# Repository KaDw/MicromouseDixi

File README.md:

# Micromouse Dixi #
	
|  |  |
| ----- | ----- |
| Width   | 79mm  |
| Length  | 95mm  |
| Weight  |   |
| Wheels  | 3D printed wheels + MZT301-20 tyres  |
| Microcontroller  | STM32F405RGT6  |
| Gear ratio  | 27:42  |
| Motor  | Pololu 5:1 HPCB  |
| Encoders  | AS55147P  |
| Battery  | Li-Pol Dualsky 7.4V 150mAh 20C  |
| Motor Driver  | TB6612FNG  |
| Sensor | TEFT4300 + SFH4545 X 6  |
| Gyro | MPU6050  |

[BOM](https://docs.google.com/spreadsheets/d/1-OBliDhJaHepW5BqGZAOIfc_tJH4ITr39Bejxq-Zry4/edit?usp=sharing)

### Development tools ###

* STM32CubeMX Version 4.17.0
* HAL Libraries - FW_F4 V1.13.1
* Keil uVision 5.21a
* EagleCAD 7.7
* Autodesk Inventor 2016

Development tools available [here](https://drive.google.com/open?id=0B6SlddUSFtelRTBFR0EwWk1qT1k)

### Setup ###

* CubeMX setup
You can get HAL libraries by going to Help->Install New Libraries->Firmware Package for Family STM32F4.
...

### Who do I talk to? ###

* Karol Trzciński k.trzcinski95@gmail.com
* Karol Dworakowski karol1dw@gmail.com

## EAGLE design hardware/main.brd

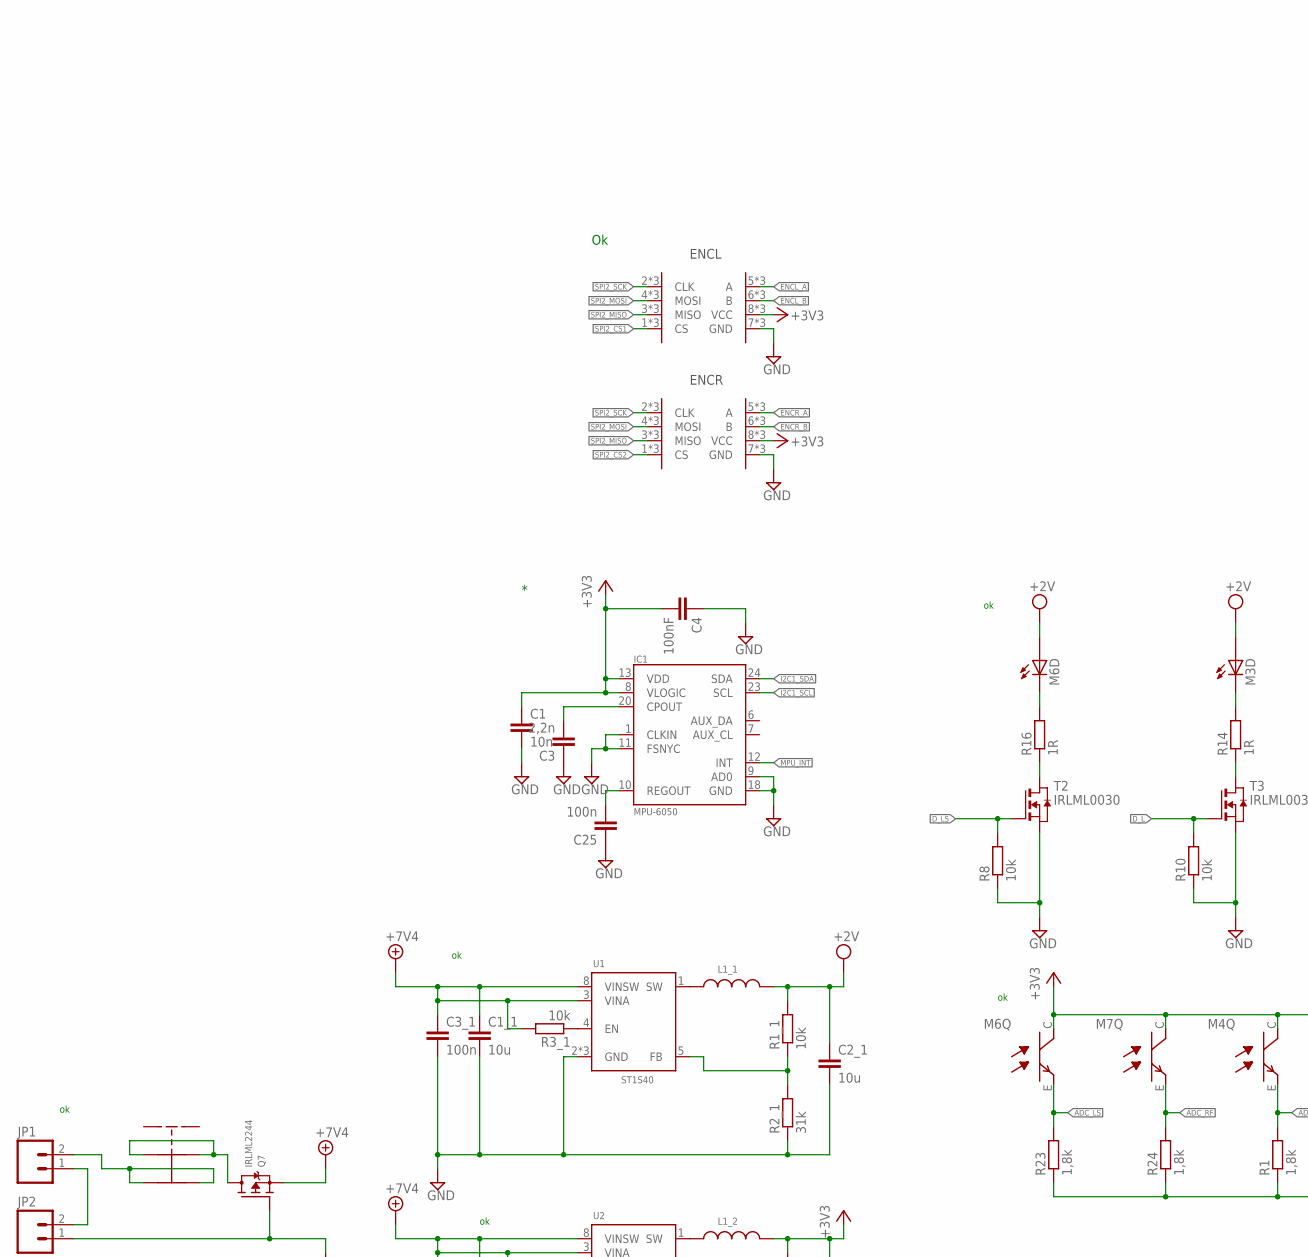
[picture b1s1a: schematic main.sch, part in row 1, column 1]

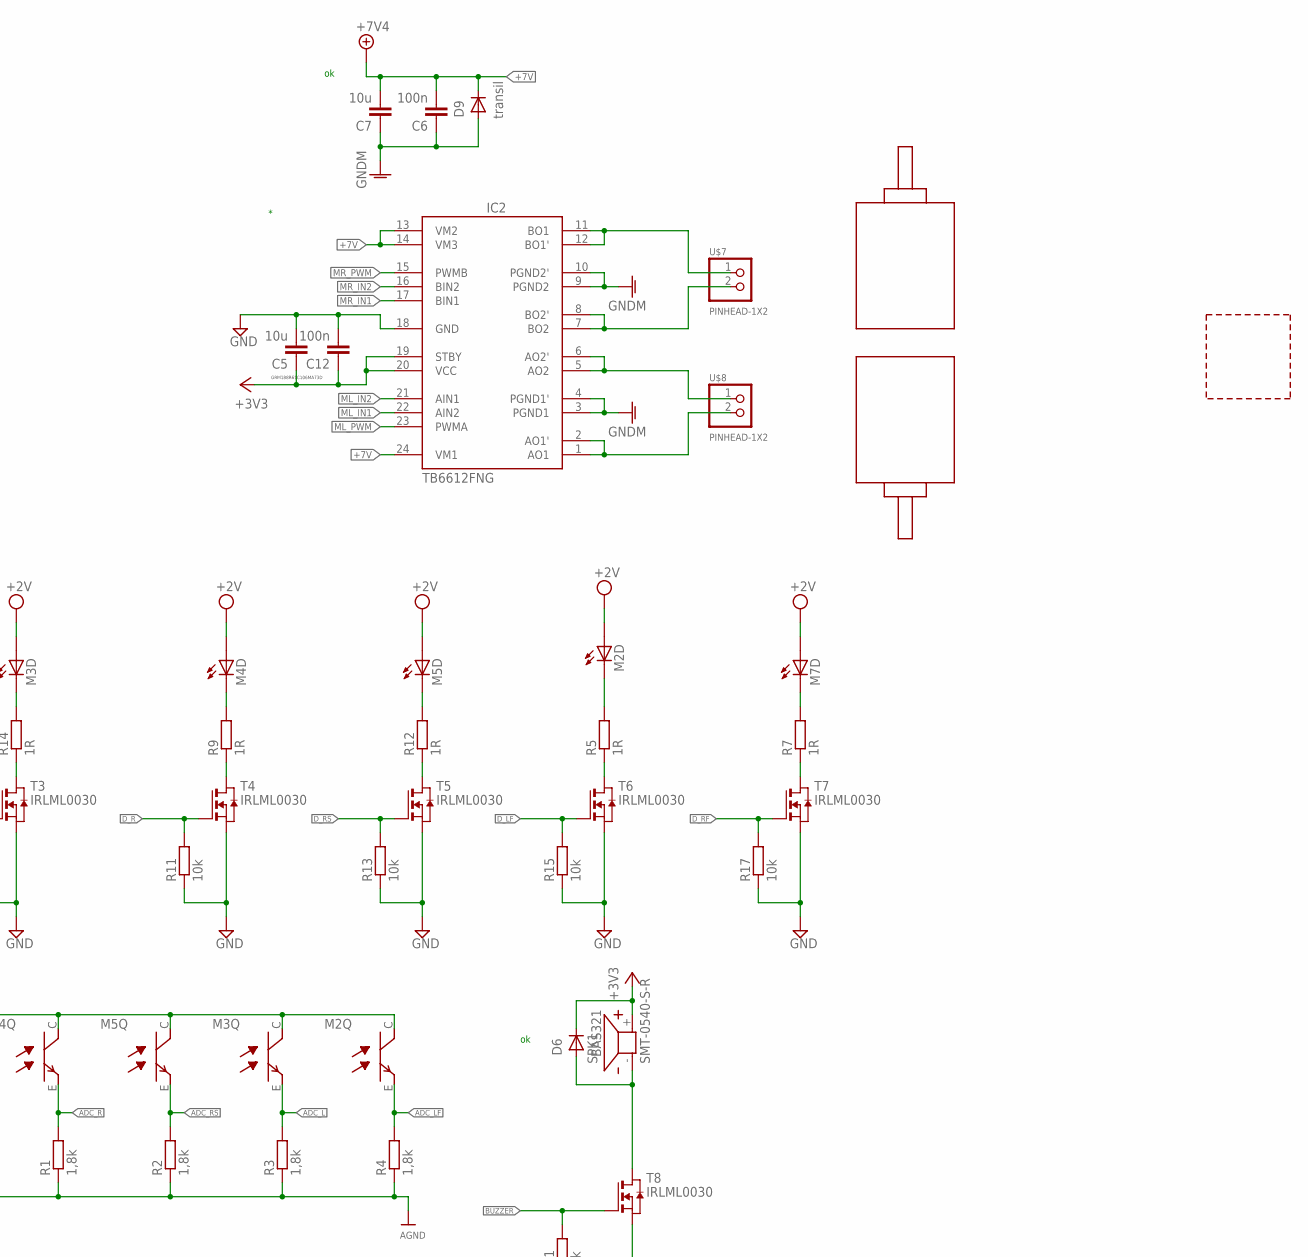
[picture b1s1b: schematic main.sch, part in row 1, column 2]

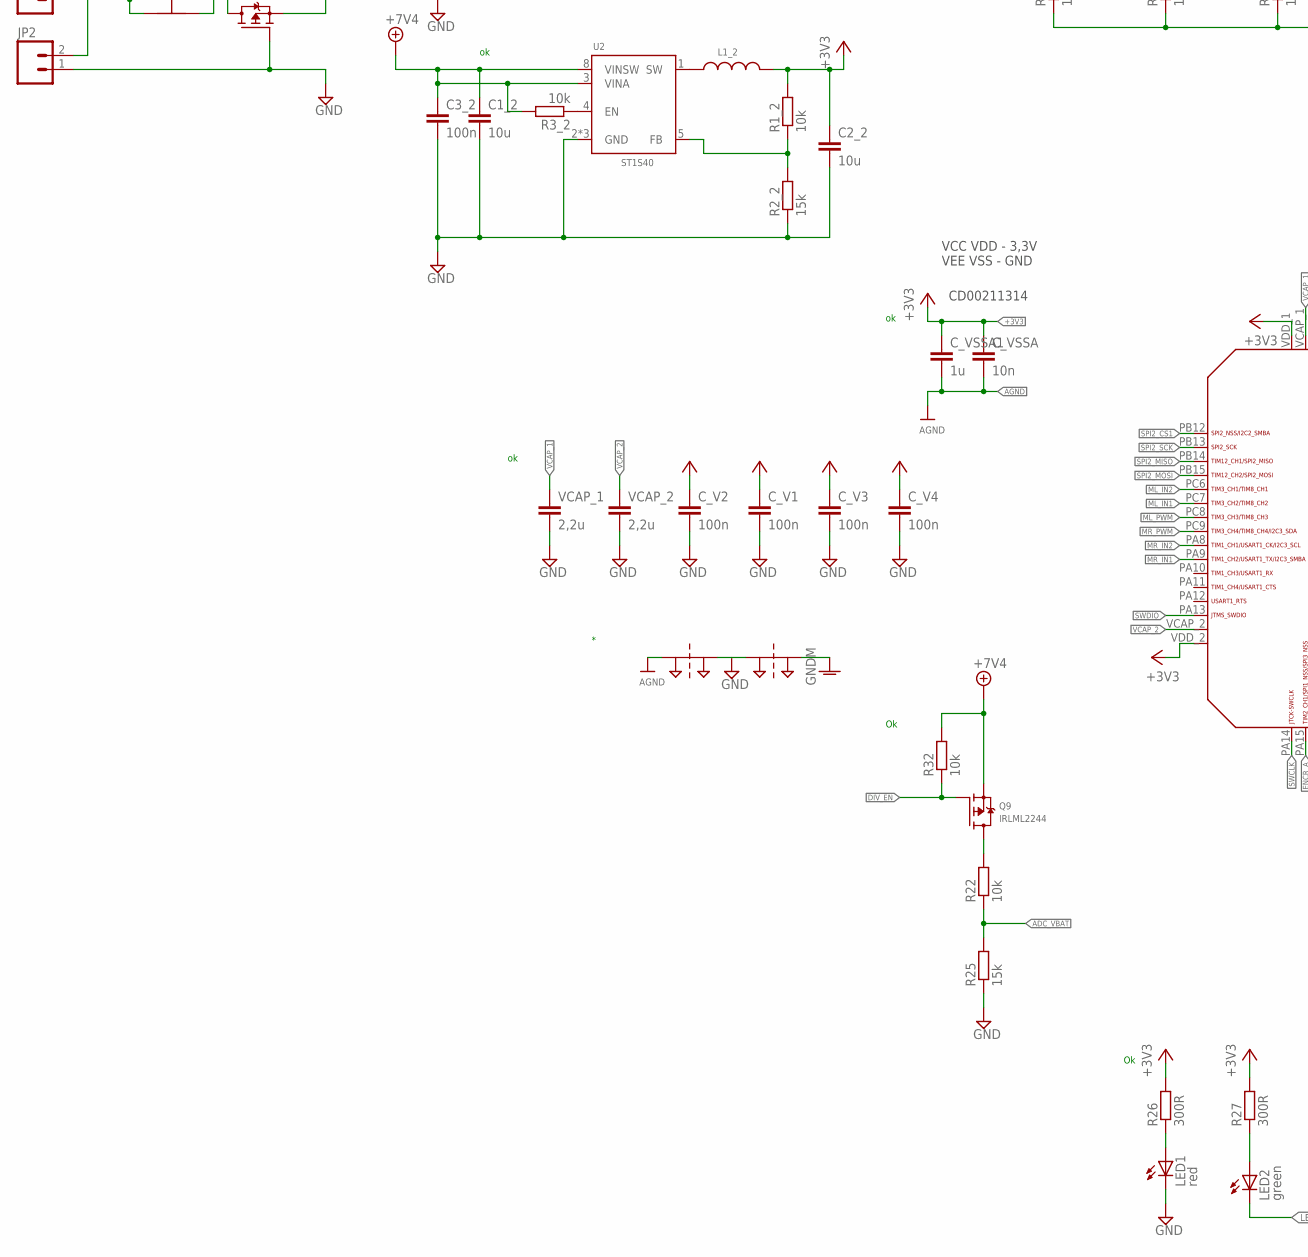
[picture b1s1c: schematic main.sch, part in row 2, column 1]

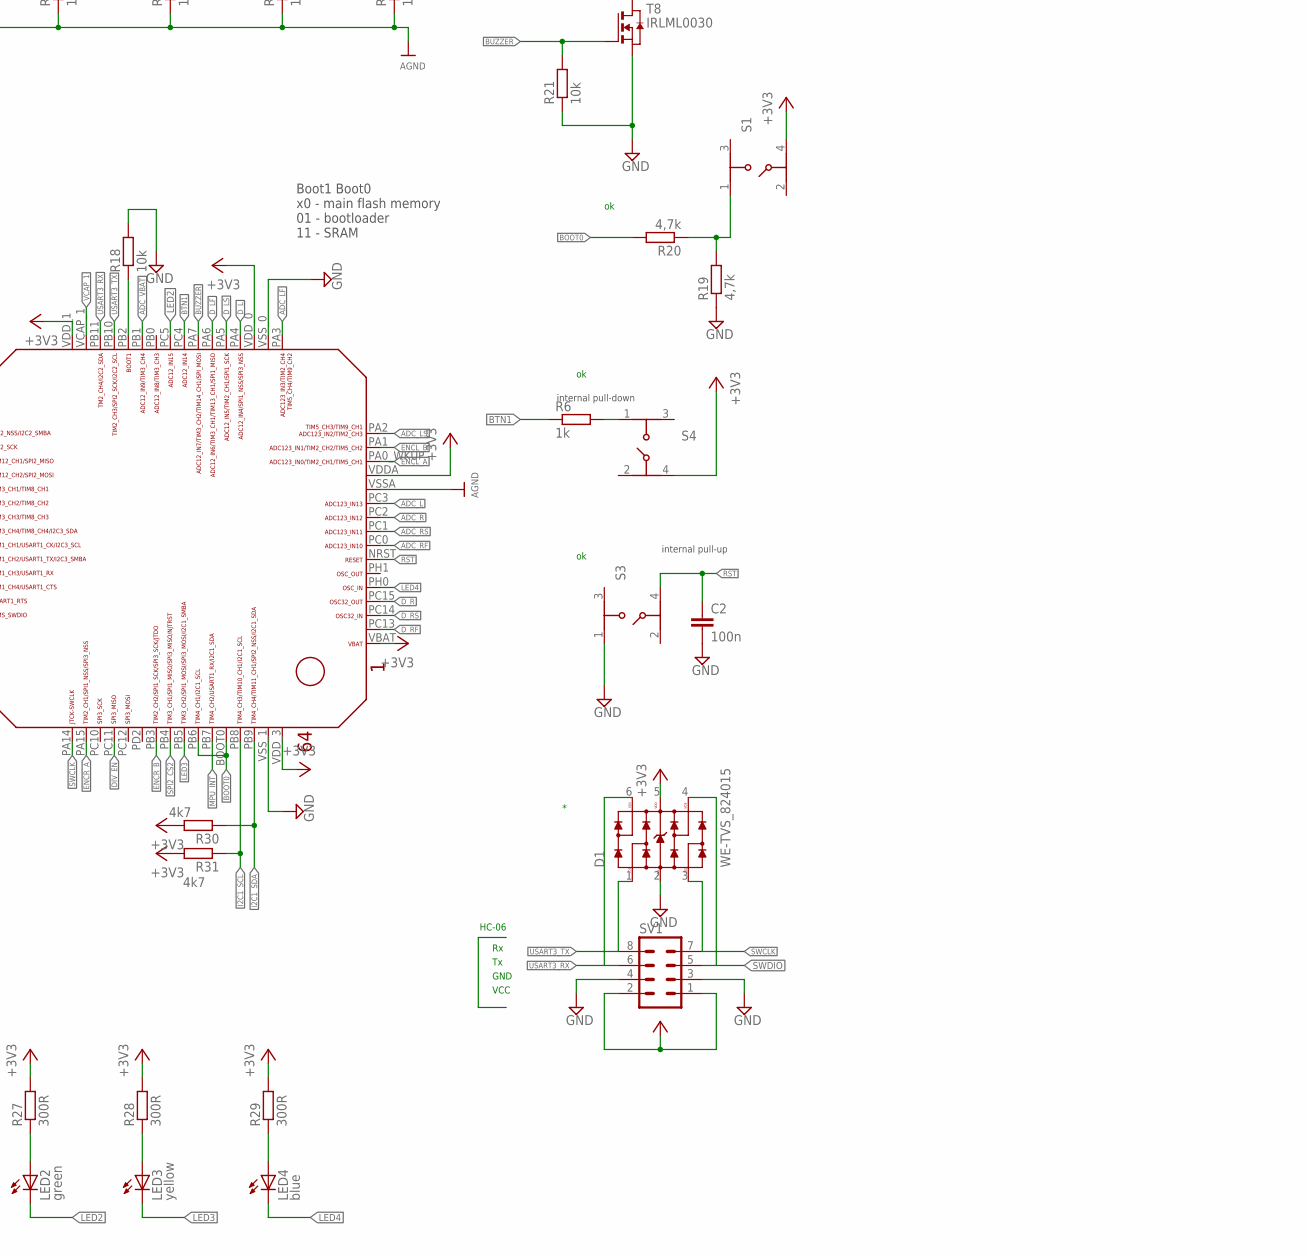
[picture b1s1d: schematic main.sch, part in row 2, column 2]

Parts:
C1: 10n; C0603
C1_1, C1_2, C5: 10u; C0805
C2, C3_1, C3_2, C6, C12, C25: 100n; C0603
C2_1, C2_2, C7: 10u; C1206
C3: 2,2n; C0603
C4: 100nF; C0603
C_V1, C_V2, C_V3, C_V4: 100n; C0603
C_VSSA: 10n; C0603
C_VSSA1: 1u; C0603
D1: WE-TVS_824015; WE-TVS_SOT23-6L
D6: BAS321; SOD323(F)
D9: transil; SOD323(F)
IC1: MPU-6050; QFN.24.4X4
IC2: TB6612FNG; SSOP24
JP1, JP2: M02POLAR; MOLEX-1X2
L1: LABITYNT; LABIRYNT
L1_1: WE-MAIA_3015_78438335068; WE-MAIA_3015
L1_2: WE-MAIA_3015_78438335033; WE-MAIA_3015
LED1: red; SML1206
LED2: green; SML1206
LED3: yellow; SML1206
LED4: blue; SML1206
M1: MOTOR_MOUNT_V2
M2, M3, M4, M5, M6, M7: LED_MOUNT
OFF: PRZELACZNIK_SUWAKOWY
PT1, PT2: 2PT_GND_TIE
Q7, Q9: IRLML2244; SOT23-R
R1, R2, R3, R4, R23, R24: 1,8k; R0603
R1_1, R1_2, R3_1, R3_2, R8, R10, R11, R13, R15, R17, R18, R21, R22, R32: 10k; R0603
R2_1: 31k; R0603
R2_2, R25: 15k; R0603
R5, R7, R9, R12, R14, R16: 1R; R0603
R6: 1k; R0603
R19, R20: 4,7k; R0603
R26, R27, R28, R29: 300R; R0603
R30, R31: 4k7; R0603
S1, S3, S4: 434153017835
SPK1: SMT-0540-S-R
SV1: MA04-2
T2, T3, T4, T5, T6, T7, T8: IRLML0030; SOT-23
U1, U2: ST1S40; SO8
U3: STM32F4X5; STM32F4-LQFP64
U$7, U$8: PINHEAD-1X2; PIHEAD-1X2
U$9, U$10: ENCODER_MOUNT
VCAP_1, VCAP_2: 2,2u; C0603

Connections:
+1.8V: C2_1.1, L1_1.2, M2.+ (A), M3.+ (A), M4.+ (A), M5.+ (A), M6.+ (A), M7.+ (A), R1_1.2
+3V3: C1.1, C2_2.1, C4.2, C5.1, C12.1, C_V1.1, C_V2.1, C_V3.1, C_V4.1, C_VSSA.1, C_VSSA1.1, D1.5 (VDD), D6.1 (K), IC1.8 (VLOGIC), IC1.13 (VDD), IC2.19 (STBY), IC2.20 (VCC), L1_2.2, M2.C, M3.C, M4.C, M5.C, M6.C, M7.C, R1_2.2, R26.2, R27.2, R28.2, R29.2, R30.2, R31.2, S1.4, S4.4, SPK1.+, SV1.1, SV1.2, U3.VBAT, U3.VDDA, U3.VDD_0, U3.VDD_1, U3.VDD_2, U3.VDD_3, U$9.8 (VCC), U$9.8_1 (VCC), U$9.8_2 (VCC), U$10.8 (VCC), U$10.8_1 (VCC), U$10.8_2 (VCC)
+7V: C1_1.1, C1_2.1, C3_1.1, C3_2.1, C6.2, C7.2, D9.1 (K), IC2.13 (VM2), IC2.14 (VM3), IC2.24 (VM1), Q7.2 (S), Q9.2 (S), R3_1.2, R3_2.2, R32.2, U1.3 (VINA), U1.8 (VINSW), U2.3 (VINA), U2.8 (VINSW)
ADC_L: M3.E, R3.2, U3.PC3
ADC_LF: M2.E, R4.2, U3.PA3
ADC_LS: M6.E, R23.2, U3.PA2
ADC_R: M4.E, R1.2, U3.PC2
ADC_RF: M7.E, R24.2, U3.PC0
ADC_RS: M5.E, R2.2, U3.PC1
ADC_VBAT: R22.1, R25.2, U3.PB1
AGND: C_VSSA.2, C_VSSA1.2, PT1.P$1, R1.1, R2.1, R3.1, R4.1, R23.1, R24.1, U3.VSSA
ASDF: R19.2, R20.1, S1.1
BOOT0: R20.2, U3.BOOT0, U3.PB6
BTN1: R6.1, U3.PC4
BUZZER: R21.2, T8.3 (G), U3.PA7
DIV_EN: Q9.1 (G), R32.1, U3.PC11
D_L: R10.2, T3.3 (G), U3.PA4
D_LF: R15.2, T6.3 (G), U3.PA6
D_LS: R8.2, T2.3 (G), U3.PA5
D_R: R11.2, T4.3 (G), U3.PC15
D_RF: R17.2, T7.3 (G), U3.PC13
D_RS: R13.2, T5.3 (G), U3.PC14
ENCL_A: U3.PA0_WKUP (PA0_AKUP), U$9.5 (A), U$9.5_1 (A), U$9.5_2 (A)
ENCL_B: U3.PA1, U$9.6 (B), U$9.6_1 (B), U$9.6_2 (B)
ENCR_A: U3.PA15, U$10.5 (A), U$10.5_1 (A), U$10.5_2 (A)
ENCR_B: U3.PB3, U$10.6 (B), U$10.6_1 (B), U$10.6_2 (B)
GND: C1.2, C1_1.2, C1_2.2, C2.2, C2_1.2, C2_2.2, C3.1, C3_1.2, C3_2.2, C4.1, C5.2, C12.2, C25.1, C_V1.2, C_V2.2, C_V3.2, C_V4.2, D1.2 (GND), IC1.1 (CLKIN), IC1.9 (AD0), IC1.11 (FSNYC), IC1.18 (GND), IC2.18 (GND), JP2.1, LED1.C, PT1.P$2, PT2.P$1, Q7.1 (G), R2_1.1, R2_2.1, R8.1, R10.1, R11.1, R13.1, R15.1, R17.1, R18.2, R19.1, R21.1, R25.1, S3.1, SV1.3, SV1.4, T2.2 (S), T3.2 (S), T4.2 (S), T5.2 (S), T6.2 (S), T7.2 (S), T8.2 (S), U1.2 (GND), U1.6 (GND), U1.7 (GND), U2.2 (GND), U2.6 (GND), U2.7 (GND), U3.VSS_0, U3.VSS_1, U$9.7 (GND), U$9.7_1 (GND), U$9.7_2 (GND), U$10.7 (GND), U$10.7_1 (GND), U$10.7_2 (GND), VCAP_1.2, VCAP_2.2
GNDA: C6.1, C7.1, D9.2 (A), IC2.3 (PGND1), IC2.4 (PGND1'), IC2.9 (PGND2), IC2.10 (PGND2'), PT2.P$2
I2C1_SCL: IC1.23 (SCL), R31.1, U3.PB8
I2C1_SDA: IC1.24 (SDA), R30.1, U3.PB9
LED2: LED2.C, U3.PC5
LED3: LED3.C, U3.PB5
LED4: LED4.C, U3.PH0
ML_IN1: IC2.22 (AIN2), U3.PC7
ML_IN2: IC2.21 (AIN1), U3.PC6
ML_PWM: IC2.23 (PWMA), U3.PC8
MPU_INT: IC1.12 (INT), U3.PB7
MR_IN1: IC2.17 (BIN1), U3.PA9
MR_IN2: IC2.16 (BIN2), U3.PA8
MR_PWM: IC2.15 (PWMB), U3.PC9
unnamed: M7.- (C), R7.2
unnamed: M2.- (C), R5.2
unnamed: R18.1, U3.PB2
unnamed: R5.1, T6.1 (D)
unnamed: R7.1, T7.1 (D)
unnamed: M4.- (C), R9.2
unnamed: R9.1, T4.1 (D)
unnamed: M5.- (C), R12.2
unnamed: R12.1, T5.1 (D)
unnamed: M3.- (C), R14.2
unnamed: R14.1, T3.1 (D)
unnamed: M6.- (C), R16.2
unnamed: R16.1, T2.1 (D)
unnamed: Q9.3 (D), R22.2
unnamed: L1_1.1, U1.1 (SW)
unnamed: L1_2.1, U2.1 (SW)
unnamed: R3_1.1, U1.4 (EN)
unnamed: R3_2.1, U2.4 (EN)
unnamed: JP1.1, JP2.2
unnamed: LED1.A, R26.1
unnamed: LED2.A, R27.1
unnamed: LED3.A, R28.1
unnamed: LED4.A, R29.1
unnamed: R6.2, S4.1
unnamed: C25.2, IC1.10 (REGOUT)
unnamed: D6.2 (A), SPK1.-, T8.1 (D)
unnamed: C3.2, IC1.20 (CPOUT)
unnamed: IC2.1 (AO1), IC2.2 (AO1'), U$8.2
unnamed: IC2.11 (BO1), IC2.12 (BO1'), U$7.1
unnamed: IC2.7 (BO2), IC2.8 (BO2'), U$7.2
unnamed: IC2.5 (AO2), IC2.6 (AO2'), U$8.1
unnamed: OFF.2, OFF.5, Q7.3 (D)
unnamed: JP1.2, OFF.3, OFF.6
unnamed: R1_2.1, R2_2.2, U2.5 (FB)
unnamed: R1_1.1, R2_1.2, U1.5 (FB)
RST: C2.1, S3.4, U3.NRST
SPI2_CS1: U3.PB12, U$9.1 (CS), U$9.1_1 (CS), U$9.1_2 (CS)
SPI2_CS2: U3.PB4, U$10.1 (CS), U$10.1_1 (CS), U$10.1_2 (CS)
SPI2_MISO: U3.PB14, U$9.3 (MISO), U$9.3_1 (MISO), U$9.3_2 (MISO), U$10.3 (MISO), U$10.3_1 (MISO), U$10.3_2 (MISO)
SPI2_MOSI: U3.PB15, U$9.4 (MOSI), U$9.4_1 (MOSI), U$9.4_2 (MOSI), U$10.4 (MOSI), U$10.4_1 (MOSI), U$10.4_2 (MOSI)
SPI2_SCK: U3.PB13, U$9.2 (CLK), U$9.2_1 (CLK), U$9.2_2 (CLK), U$10.2 (CLK), U$10.2_1 (CLK), U$10.2_2 (CLK)
SWCLK: D1.3, SV1.7, U3.PA14
SWDIO: D1.4, SV1.5, U3.PA13
USART3_RX: D1.6, SV1.6, U3.PB11
USART3_TX: D1.1, SV1.8, U3.PB10
VCAP_1: U3.VCAP_1, VCAP_1.1
VCAP_2: U3.VCAP_2, VCAP_2.1

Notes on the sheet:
Boot1 Boot0 x0 - main flash memory 01 - bootloader 11 - SRAM
VCC VDD - 3,3V VEE VSS - GND
internal pull-up
internal pull-down
GND
VCC
HC-06
ENCR
ENCL
CD00211314
GRM188R61C106MA73D

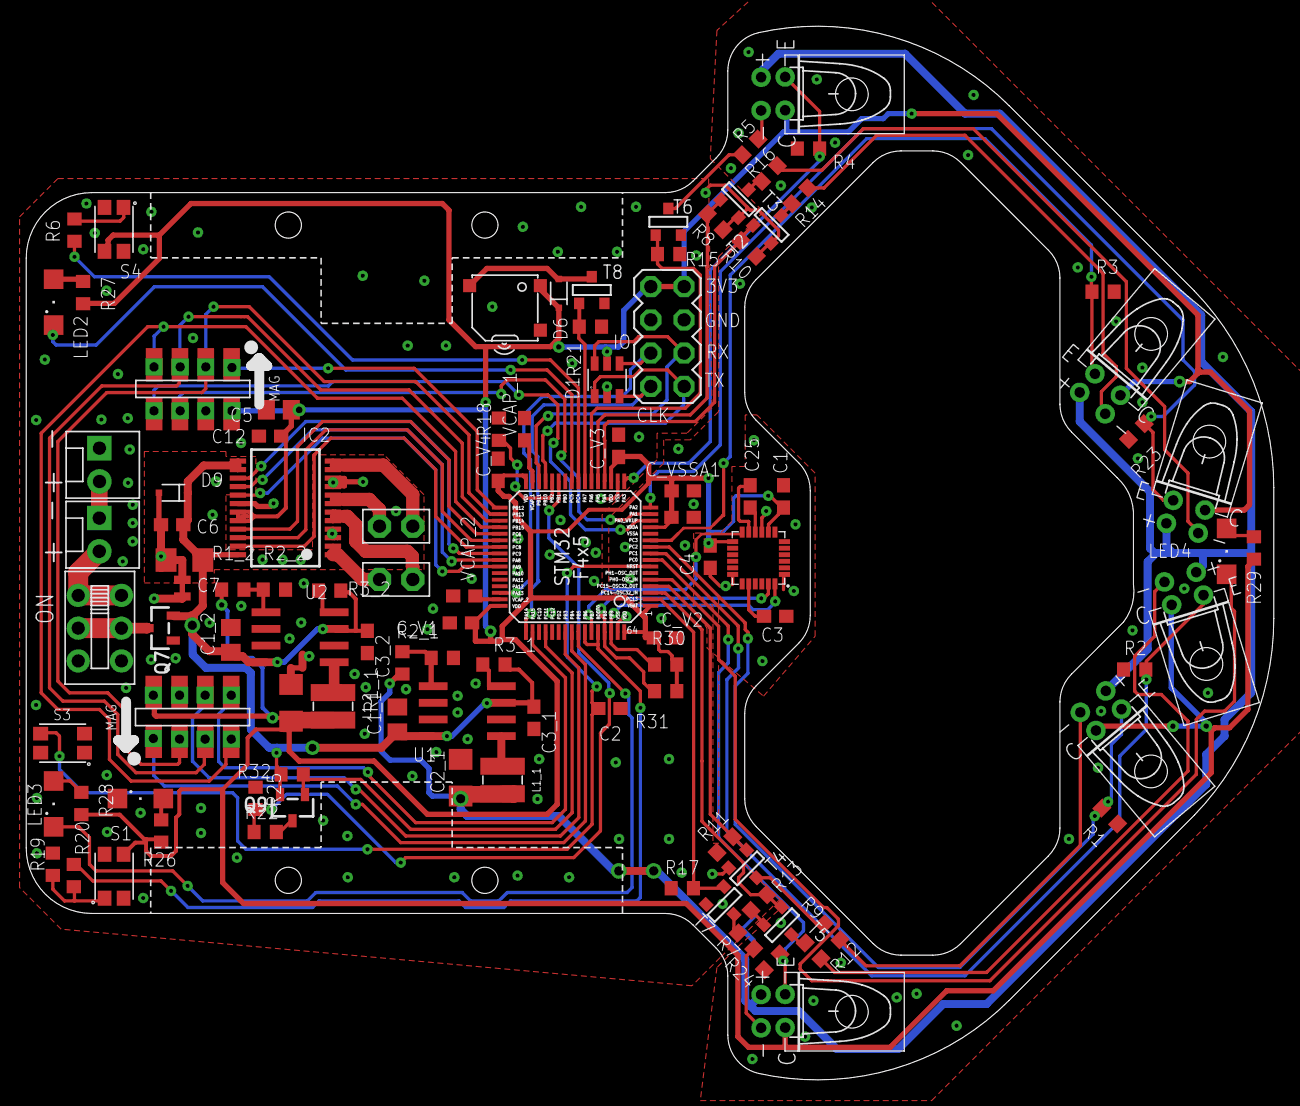
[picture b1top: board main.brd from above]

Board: 2 copper layers, 95.1 x 80.3 mm, 106 parts (1 on the bottom side), 87 nets.

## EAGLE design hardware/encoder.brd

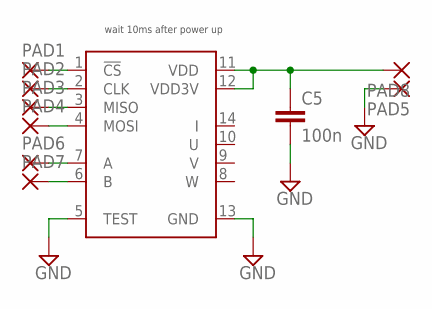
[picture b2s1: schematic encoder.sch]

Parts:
C5: 100n; C0603
PAD1, PAD2, PAD3, PAD4, PAD5, PAD6, PAD7, PAD8: SMD2; SMD1,27-2,54
U$1: AS5147P; TSSOP-14

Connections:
A: PAD6.1, U$1.7 (A)
B: PAD7.1, U$1.6 (B)
CLK: PAD2.1, U$1.2 (CLK)
CS: PAD1.1, U$1.1 (!CS)
GND: C5.2, PAD5.1, U$1.5 (TEST), U$1.13 (GND)
MISO: PAD3.1, U$1.3 (MISO)
MOSI: PAD4.1, U$1.4 (MOSI)
VCC: C5.1, PAD8.1, U$1.11 (VDD), U$1.12 (VDD3V)

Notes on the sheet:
wait 10ms after power up

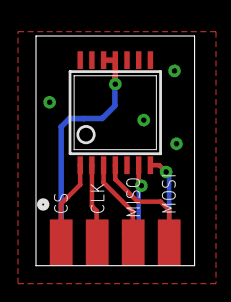
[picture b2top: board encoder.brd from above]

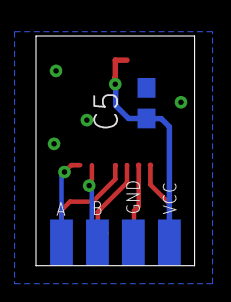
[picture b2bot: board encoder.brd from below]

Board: 2 copper layers, 8.8 x 12.8 mm, 10 parts (5 on the bottom side), 8 nets.

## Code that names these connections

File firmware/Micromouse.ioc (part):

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Mcu.Name=STM32F405RGTx
Mcu.Package=LQFP64
Mcu.UserName=STM32F405RGTx
PA0-WKUP.GPIOParameters=GPIO_Label
PA0-WKUP.GPIO_Label=ENCL_A
PA0-WKUP.Signal=S_TIM5_CH1
PA1.GPIOParameters=GPIO_Label
PA1.GPIO_Label=ENCL_B
PA1.Signal=S_TIM5_CH2
PA13.Mode=Serial_Wire
PA13.Signal=SYS_JTMS-SWDIO
PA14.Mode=Serial_Wire
PA14.Signal=SYS_JTCK-SWCLK
PA15.GPIOParameters=GPIO_Label
PA15.GPIO_Label=ENCR_A
PA15.Signal=S_TIM2_CH1_ETR
PA2.GPIOParameters=GPIO_Label
PA2.GPIO_Label=ADC_LS
PA2.Signal=ADCx_IN2
PA3.GPIOParameters=GPIO_Label
PA3.GPIO_Label=ADC_LF
PA3.Signal=ADCx_IN3
PA4.GPIOParameters=GPIO_PuPd,GPIO_Label
PA4.GPIO_Label=D_L
PA4.GPIO_PuPd=GPIO_PULLDOWN
PA4.Signal=GPIO_Output
PA5.GPIOParameters=GPIO_PuPd,GPIO_Label
PA5.GPIO_Label=D_LS
PA5.GPIO_PuPd=GPIO_PULLDOWN
PA5.Signal=GPIO_Output
PA6.GPIOParameters=GPIO_PuPd,GPIO_Label
PA6.GPIO_Label=D_LF
PA6.GPIO_PuPd=GPIO_PULLDOWN
PA6.Signal=GPIO_Output
PA7.GPIOParameters=GPIO_PuPd,GPIO_Label
PA7.GPIO_Label=BUZZER
PA7.GPIO_PuPd=GPIO_PULLDOWN
PA7.Signal=GPIO_Output
PA8.GPIOParameters=GPIO_Label
PA8.GPIO_Label=MR_IN2
PA8.Signal=GPIO_Output
PA9.GPIOParameters=GPIO_Label
PA9.GPIO_Label=MR_IN1
PA9.Signal=GPIO_Output
PB1.GPIOParameters=GPIO_Label
PB1.GPIO_Label=ADC_VBAT
PB1.Signal=ADCx_IN9
PB10.Mode=Asynchronous
PB10.Signal=USART3_TX
PB11.Mode=Asynchronous
PB11.Signal=USART3_RX
PB12.GPIOParameters=PinState,GPIO_PuPd,GPIO_Label
PB12.GPIO_Label=SPI2_CS1
PB12.GPIO_PuPd=GPIO_PULLUP
PB12.PinState=GPIO_PIN_SET
PB12.Signal=GPIO_Output
PB13.Mode=Full_Duplex_Master
PB13.Signal=SPI2_SCK
PB14.Mode=Full_Duplex_Master
PB14.Signal=SPI2_MISO
PB15.Mode=Full_Duplex_Master
PB15.Signal=SPI2_MOSI
PB3.GPIOParameters=GPIO_Label
PB3.GPIO_Label=ENCR_B
PB3.Signal=S_TIM2_CH2
PB4.GPIOParameters=PinState,GPIO_PuPd,GPIO_Label
PB4.GPIO_Label=SPI2_CS2
PB4.GPIO_PuPd=GPIO_PULLUP
PB4.PinState=GPIO_PIN_SET
PB4.Signal=GPIO_Output
PB6.GPIOParameters=GPIO_Label
PB6.GPIO_Label=BTN2
PB6.Signal=GPIO_Input
PB7.GPIOParameters=GPIO_Label
PB7.GPIO_Label=MPU_INT
PB7.Signal=GPIO_Input
PB8.Mode=I2C
PB8.Signal=I2C1_SCL
PB9.Mode=I2C
PB9.Signal=I2C1_SDA
PC0.GPIOParameters=GPIO_Label
PC0.GPIO_Label=ADC_RF
PC0.Signal=ADCx_IN10
PC1.GPIOParameters=GPIO_Label
PC1.GPIO_Label=ADC_RS
PC1.Signal=ADCx_IN11
PC11.GPIOParameters=GPIO_PuPd,GPIO_Label
PC11.GPIO_Label=DIV_EN
PC11.GPIO_PuPd=GPIO_PULLDOWN
PC11.Signal=GPIO_Output
PC12.GPIOParameters=PinState,GPIO_Label
PC12.GPIO_Label=LED3
PC12.PinState=GPIO_PIN_SET
PC12.Signal=GPIO_Output
PC13-ANTI_TAMP.GPIOParameters=GPIO_PuPd,GPIO_Label
PC13-ANTI_TAMP.GPIO_Label=D_RF
PC13-ANTI_TAMP.GPIO_PuPd=GPIO_PULLDOWN
PC13-ANTI_TAMP.Signal=GPIO_Output
PC14-OSC32_IN.GPIOParameters=GPIO_PuPd,GPIO_Label
PC14-OSC32_IN.GPIO_Label=D_RS
PC14-OSC32_IN.GPIO_PuPd=GPIO_PULLDOWN
PC14-OSC32_IN.Signal=GPIO_Output
PC15-OSC32_OUT.GPIOParameters=GPIO_PuPd,GPIO_Label
PC15-OSC32_OUT.GPIO_Label=D_R
PC15-OSC32_OUT.GPIO_PuPd=GPIO_PULLDOWN
PC15-OSC32_OUT.Signal=GPIO_Output
PC2.GPIOParameters=GPIO_Label
PC2.GPIO_Label=ADC_R
PC2.Signal=ADCx_IN12
PC3.GPIOParameters=GPIO_Label
PC3.GPIO_Label=ADC_L
PC3.Signal=ADCx_IN13
PC4.GPIOParameters=GPIO_Label
PC4.GPIO_Label=BTN1
PC4.Signal=GPIO_Input
PC5.GPIOParameters=PinState,GPIO_Label
PC5.GPIO_Label=LED2
PC5.PinState=GPIO_PIN_SET
PC5.Signal=GPIO_Output
PC6.GPIOParameters=GPIO_Label
PC6.GPIO_Label=ML_IN1
PC6.Signal=GPIO_Output
PC7.GPIOParameters=GPIO_Label
PC7.GPIO_Label=ML_IN2
PC7.Signal=GPIO_Output
PC8.GPIOParameters=GPIO_Label
PC8.GPIO_Label=ML_PWM
PC8.Signal=S_TIM3_CH3
PC9.GPIOParameters=GPIO_Label
PC9.GPIO_Label=MR_PWM
PC9.Signal=S_TIM3_CH4
PH0-OSC_IN.GPIOParameters=PinState,GPIO_Label
PH0-OSC_IN.GPIO_Label=LED4
PH0-OSC_IN.PinState=GPIO_PIN_SET
PH0-OSC_IN.Signal=GPIO_Output
RCC.HSE_VALUE=8000000
RCC.SYSCLKFreq_VALUE=168000000
RCC.SYSCLKSource=RCC_SYSCLKSOURCE_PLLCLK
board=Micromouse

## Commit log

2017-05-29 initial commit, first 3d model
2017-06-04 added sch
2017-06-04 added eagle lbrs
2017-06-05 schematic...
2017-06-07 cleanup, 3d top mount
2017-06-07 encoder brd
2017-06-11 fixed 3d model
2017-06-23 test
2017-06-24 added led_mount to model, pcb elemets grouped
2017-06-26 power supply layout almost done
2017-06-29 pcb 29.06
2017-06-29 pcb 29.06 1
2017-06-29 pcb todo front layout
2017-06-29 led mount fix
2017-06-29 Rozmieszczone diody na dziobie, przelotki przy DCDC
2017-06-30 3d model - v1, gnd plane fun
2017-06-30 updated picture
2017-06-30 almost done, gnd mess
2017-07-01 led resistors changed to 0603, fixed gnd plane
2017-07-01 polygons fix
2017-07-02 porzadek z polygonami
2017-07-02 dodanie lini od przerwania od MPU, dodanie C na DCDC 3V3, laczenie GNDA GND i GNDM, dodanie diod ESD na programator, rewizja
2017-07-03 encoder lbr fix, connected gnd
2017-07-04 bugfix: mosfet przy zasilaniu
2017-07-04 poprawa 1 sciezki przy bateii
2017-07-05 dodanie napisow, odsuniecie kilku sciezek od krawedzi plytki, minimlne zmniejszenie otworu z przodu (aby nie bylo problemu z odlegloscia od krawedzi)
2017-07-26 poukladanie warstwy opisowej, dodanie przelotek - wersja finalna
2017-08-27 changed wheel shaft size to 3mm
2017-09-14 dodanie wartosci elementow
2017-09-14 wygenerowany kod
2017-09-14 zarys wielobuforowego loggera wiadomosci, bezpiecznego w przerwaniach
2017-09-18 cleanup, .gitignore fixed
2017-09-21 as5147p spi_read working (ugly code)
2017-09-21 as5147p cleanup
2017-09-25 mpu_selftest, mpu_init added
2017-09-29 logger przechodzi testy
2017-09-30 dodanie kodu odpowiedzialnego za UI, ujednolicanie nazwinictwa plikow
2017-10-02 dodanie komentarzy
2017-10-02 dodanie FIFO opartego na makrach
2017-10-03 fifo przechodzi testy i posiada wiecej komentarzy
2017-10-03 lepiej podawac obiekty, a nie wskazniki do push, pop, peek, testy z elementami tablicowymi
2017-10-04 fifo-dodawanie poprzez element a nie wskaznik, dodanie ring
2017-10-06 returns fixed, gyro using dma
2017-10-06 integracja z eclipse
2017-10-06 powiazanie UI i hardwaru, testow na pc oraz testow na hardware
2017-10-06 uaktualnienie projektu z CubeMX - dodanie DMA do UART i tim10
2017-10-06 imu hardware offset registers
2017-10-07 do przetestowania na mm
2017-10-07 projekt testowania na PC
2017-10-10 logger test pass
2017-10-12 added fusion file
2017-10-12 added pin description to encoders
2017-10-12 gyro vlogic fixed
2017-10-12 dodanie mymain
2017-10-12 wstepna wersja oblugi silnikow
2017-10-13 hole sizes fixed for 3d print
2017-10-13 dodawanie komentarzy, ujednolicanie kodu
2017-10-14 poczatek alg symulowania modelu dynamicznego
2017-10-15 wheel with gear
2017-10-18 ir led test setup
2017-10-19 dodanie symulatora oraz sieci modulow dynamicznych
2017-10-21 more ir led testing
2017-10-24 wyszukiwanie modelu matematyczne
2017-10-26 mpu6050 without fifo
2017-10-27 wyswietlanie mapy modulow oraz printowanie spisu polaczen w sieci modulow
2017-10-29 gyro fixed
2017-10-29 dodanie symulatora dynamiki jazdy oraz SLAM
2017-10-31 pull-downs added, sensor_off
2017-11-01 symulator dynamiki+SLAM+profiler- zarys
2017-11-01 regulator polarny
2017-11-03 Dodanie Tourney Selection, try przy update_module i losowanie paramatrow jako 1/(random()-0.5
2017-11-03 dodanie mutowanie podczas rozmnazania czlonkow tej samej rodziny
2017-11-03 Poprawa kluczowych bledow - zejscie z bledem do zera!
2017-11-03 dodanie optymalizatora liniowe do GA
2017-11-04 logger fix
2017-11-09 interaktywna wersja symulatora
2017-11-10 added UI buttons handling, small fixes in logger
2017-11-15 model 1-rzedu
2017-11-17 dzialajacy model kinamtyczny i dynamiczny + tester regulatora
2017-11-23 brudny commit
2017-11-24 ion fix
2017-11-25 Dodanie symulatora w wersji RPN
2017-11-26 dodanie integratora eulera
2017-11-26 usuniecie bledu przu usuwanie zmiennej (mutacji SimulattorRPN)
2017-11-26 naprawa cross - blad po simulatorRPN.mutate
2017-11-26 naprawa bledow po mutacji, dodanie RPN.simplify()
2017-12-02 wersja od rysunkow - dzialajacy symulator modulowy
2017-12-11 wesja do inz
2017-12-11 dodanie regulatora liniowego
2018-01-05 fixed boot0 button, buzzer footprint, togh matches 3d model
2018-03-30 added mosfet pulldowns (IR leds), PB2 pulldown
2018-03-30 fixed silkcreen covering pads
2018-04-01 more pcb fixes
2018-04-08 dodanie profilera
2018-05-26 redesigned drive part
2018-05-26 added *.lck files to gitignore
2018-05-26 finally fixed .lck and .onetoc2 bullshit
2018-05-27 pcb matches the 3d model
2018-08-02 updated Dixi.iam
2018-08-21 fixed gnd connection for C1_1 and C1_2 caps (dc converter)
2018-08-22 moved step down converters closer to battery
2018-12-10 add more GND vias, models

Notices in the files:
parts and their libraries:
microbuilder: This work is placed in the public domain, and may be freely used for commercial and non-commercial work with the following conditions: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
EAGLE-AECQ_PRODUCTS-rev17b: Copyright: Würth Elektronik
